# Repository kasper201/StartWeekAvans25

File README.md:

# StartWeekAvans25

The StartWeekAvans25 project is made to provide a playable game for the firstyears during the startweek. It is a continuation from [previous year's project](https://github.com/JaroWMR/Startweek.git).

# Getting Started
There are two parts to this project, the Zephyr project and Qt project.
The Zephyr project is the code which will run on the hardware and the Qt project is the code which will run on the user's PC to provide an easy way to configure and communicate with the hardware.

## Zephyr
This project has been made with Zephyr 3.7 and SDK version 16.5.

To get started you can follow the [getting started](https://docs.zephyrproject.org/3.7.0/develop/getting_started/index.html) from Zephyr, which guides you to the install process and how you can build a project.

### Digital twin
A digital twin of the hardware has been created which simulates large parts of the hardware, to allow coding and testing without the hardware. 

#### Digital twin limitations and bugs
There are some limitations on what can and cannot be done. Those can be found [here](https://docs.zephyrproject.org/3.7.0/boards/native/doc/arch_soc.html#important-limitations).

It's very likely that a busy wait loop exists in the code if the simulator hangs. This can be prevented by a adding a 'k_sleep(K_MSEC(1));' or 'k_cpu_idle();' in the loop, or using native_loop() in the code which handles adding that for the hardware only.

Currently there is also a bug with timers, meaning that the digital twin goes through a timer faster or slower. This prevents some minigames from being played properly.

The bug is less noticable in the stand-alone version, which can be found on the "stand-alone_native_sim" branch. Please check out the readme in that branch for more information about this version.

## Qt
[//]: # (Never)
The Qt application has been made with Qt 5.12. This can be installed and has been confirmed to build on both Windows and Linux.

# Building
The Zephyr project can be either build for the hardware board or for the simulator.
You can build for the hardware as follows:
```
west build -b nucleo_h743zi [whereYouveClonedTheGitRepo]\StartWeekAvans25\Project
```
You can also do a pristine build, which clears the build folder first before building everything from 0 again:
```
west build -p -b nucleo_h743zi [whereYouveClonedTheGitRepo]\StartWeekAvans25\Project
```

You can build the project the same way for the digital twin, by just replacing the board with the digital twin's board name:
```
west build -b native_sim [whereYouveClonedTheGitRepo]\StartWeekAvans25\Project
```

# Flashing and running
[//]: # (Gonna)
## Hardware
### Prerequisites
Flashing the hardware with "west flash" requires an additional step first. You need to apply the git patch called "openocd.patch" to your Zephyr install. This can be done by following these steps:
- Download openocd.patch
- Place it in your zephyr folder
- Open the terminal, go to your zephyr folder and apply the patch with
```
git apply openocd.patch
```

After this you can program the hardware aslong as it's in bootloader mode. You can turn the hardware into bootloader mode with the following steps:

- Turn off the hardware (disconnect the battery and usb)
- Connect the debugger
- Press the Boot0 button
- Turn on the hardware 
Now the hardware is in bootloader mode and can be programmed with "west flash". 

## Digital twin
[//]: # (Give)
The digital twin can be ran on Linux machines. It has been tested and confirmed to work on Ubuntu 20.04, and also confirmed to display nothing on Arch and WSL2.
You can start it up simply by using this command from the same folder you've used "west build" in:
```
west build -t run
```

# Debugging
Both the hardware and digital twin can be debugged with GDB.
## Hardware
The nucleo board requires the STM32 gdb server and command-line toolset, which can be downloaded [from here](https://www.st.com/en/development-tools/stm32cubeclt.html?ecmp=tt9470_gl_link_feb2019&rt=um&id=UM3088). After installing the tools you can use them to set up the server and client like this:
```
Client:
arm-none-eabi-gdb.exe

Server:
ST-LINK_gdbserver.exe -d -v -t -g -cp C:\ST\STM32CubeCLT_1.18.0\STM32CubeProgrammer\bin

```

Extra documentation about the command-line tools can be found on [st's website](https://www.st.com/en/development-tools/stm32cubeclt.html?ecmp=tt9470_gl_link_feb2019&rt=um&id=UM3088#documentation).

## Digital twin
[//]: # (You)
```
gdb ./build/zephyr/zephyr.exe
```

# Testing
[//]: # (Up)
There are two ways to test this project, manual for games and automatic for all other parts of the code.
Manual testing can be enabled by setting "CONFIG_TESTMODE" to "y" in the prj.conf. After building and flashing the project as usual you'll get to see a minigame selector on the LCD. You can use the ABC buttons to navigate between minigames and use the start button to confirm the game to test.

Automatic testing is done with the help of ztests. You can build them with:
```
west build -b nucleo_h743zi [whereYouveClonedTheGitRepo]\StartWeekAvans25\Project\tests
```
Upon flashing the software on the hardware it'll start to do every selected test in a random order.
Currently the test's prj.conf is configured to test everything aside from the minigame.

You can also use Twister, Zephyr's Test Runner, to run the tests with.

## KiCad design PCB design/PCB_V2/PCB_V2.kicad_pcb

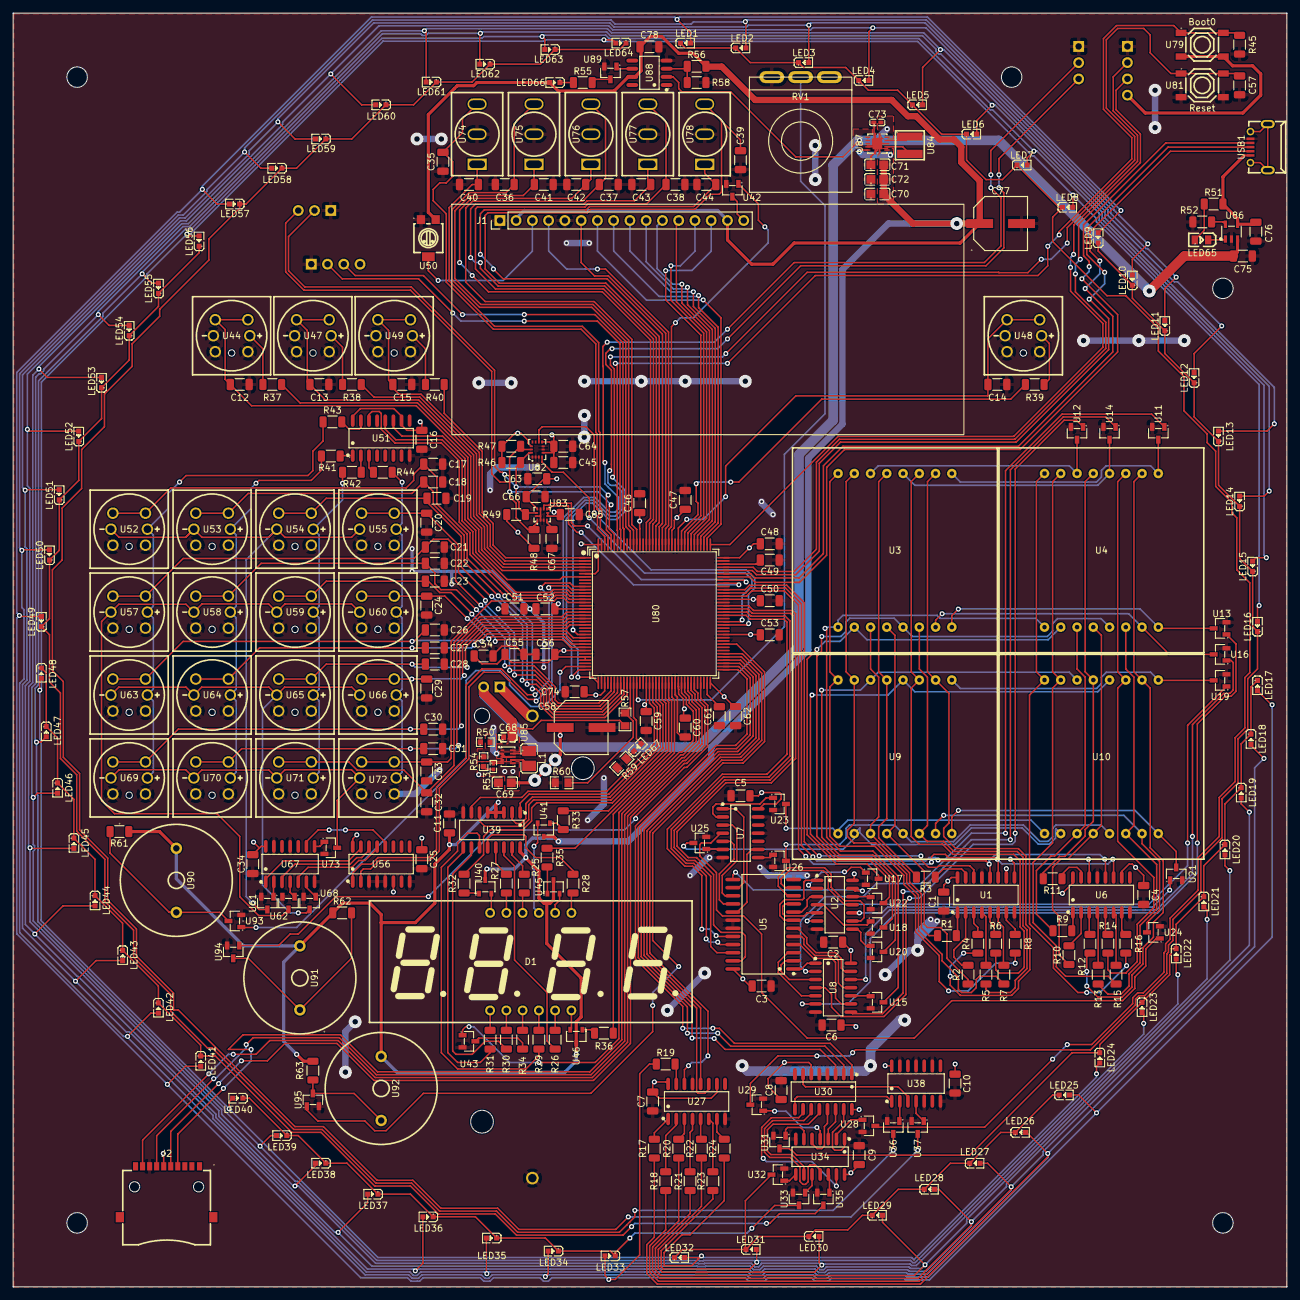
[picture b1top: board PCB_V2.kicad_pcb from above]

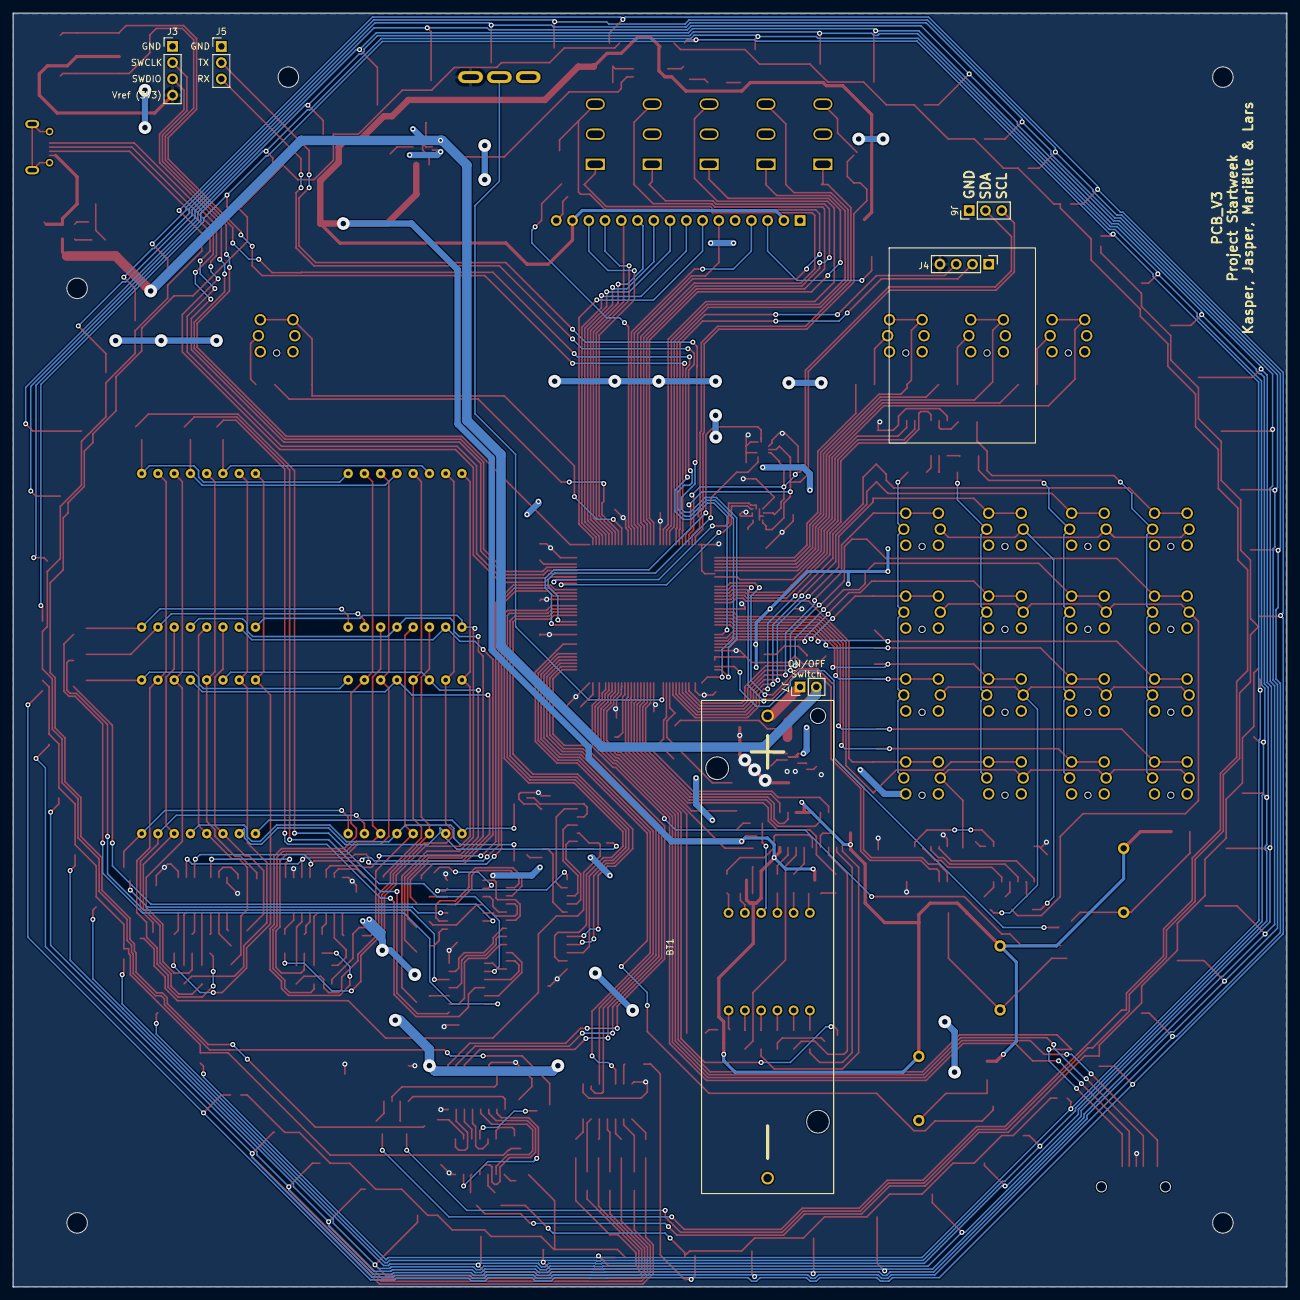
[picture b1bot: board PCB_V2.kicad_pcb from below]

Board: 2 copper layers, 199.0 x 199.0 mm, 315 parts (6 on the bottom side), 296 nets.

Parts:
BT1: Battery_Cell; Battery_Holder_Avans
C1, C2, C3, C4, C5, C6, C7, C8, C9, C10, C11, C12, C13, C14, C15, C16, C17, C18, C19, C20, C21, C22, C23, C24, C25, C26, C27, C28, C29, C30, C31, C32, C33, C34, C35, C36, C37, C38, C39, C40, C41, C42, C43, C44, C45, C46, C47, C48, C50, C52, C53, C55, C56, C57, C58, C59, C60, C62, C63, C64, C66, C67, C78: 100n; C_1206_3216Metric
C49, C61: 2u2; C_1206_3216Metric
C51, C75, C76: 4u7; C_1206_3216Metric
C54, C65: 1u; C_1206_3216Metric
C68: GRM188R60J226MEA0D; C0603
C69: GRM21BR61A226ME44L; C0805
C70, C71, C72: LMK212BJ106KG-T; C0805
C73: GRJ155R60J106ME11D; C0402
C74, C77: RVE1A471M0810; CAP-SMD_BD8.0-L8.3-W8.3-FD
D1: FJ5461BH-pure-red; LED-SEG-TH_FJ5461AH
J1: Conn_01x16; LCD_Display_AVANS
J2: SD-01A; SD-SMD_SD-01A
J3: Conn_01x04; PinHeader_1x04_P2.54mm_Vertical
J4: Conn_01x04; GPS_AVANS
J5, J6: Conn_01x03; PinHeader_1x03_P2.54mm_Vertical
J7: Conn_01x02; PinHeader_1x02_P2.54mm_Vertical
L1: LQM2HPNR47MG0L; L1008
LED1, LED2, LED3, LED4, LED5, LED6, LED7, LED8, LED9, LED10, LED11, LED12, LED13, LED14, LED15, LED16, LED17, LED18, LED19, LED20, LED21, LED22, LED23, LED24, LED25, LED26, LED27, LED28, LED29, LED30, LED31, LED32, LED33, LED34, LED35, LED36, LED37, LED38, LED39, LED40, LED41, LED42, LED43, LED44, LED45, LED46, LED47, LED48, LED49, LED50, LED51, LED52, LED53, LED54, LED55, LED56, LED57, LED58, LED59, LED60, LED61, LED62, LED63, LED64, LED66, LED67: KT-0603R; LED0603-RD
LED65: 17-21SUYC_TR8; LED0805-R-RD
R1, R2, R3, R4, R5, R6, R7, R8, R9, R10, R11, R12, R13, R14, R15, R16: 220; R_1206_3216Metric
R17, R18, R19, R20, R21, R22, R23, R24: 100; R_1206_3216Metric
R25, R26, R27, R28, R29, R30, R31, R34: 270; R_1206_3216Metric
R32, R33, R35, R36: 390; R_1206_3216Metric
R37, R38, R39, R40, R41, R42, R43, R44: 150; R_1206_3216Metric
R45, R46, R47, R48, R49: 10k; R_1206_3216Metric
R50: RC0603FR-0791KL; R0603
R51: 330; R_1206_3216Metric
R52: 2k2; R_1206_3216Metric
R53: CRCW0402100KFKED; R0402
R54: RC0603FR-07511KL; R0603
R55, R61, R62, R63: 470; R_1206_3216Metric
R56: 16k; R_1206_3216Metric
R57: 10k; R0805
R58: 20k; R_1206_3216Metric
R59: 200; R0805
R60: 18k; R0805
RV1: 50k; Potmeter_THT_Avans
U1, U6, U27, U51: SN74HC595DR; SOIC-16_L9.9-W3.9-P1.27-LS6.0-BL
U2, U7, U8, U34, U38, U67: SN74HC04DR; SOIC-14_L8.7-W3.9-P1.27-LS6.0-BL
U3, U4, U9, U10: SZ421288N_64; LED-SEG-TH_SZ421288N-64
U5: CD74HC154M96; SOIC-24_L15.4-W7.5-P1.27-LS10.3-BL
U11, U12, U13, U14, U15, U16, U17, U18, U19, U20, U21, U22, U23, U24, U25, U26, U28, U29, U31, U32, U33, U35, U36, U37, U42, U43, U61, U62, U68, U73, U89, U93, U94, U95: BSN20BKR; SOT-23-3_L2.9-W1.3-P1.90-LS2.4-BR
U30, U56: SN74HC138DR; SOIC-16_L9.9-W3.9-P1.27-LS6.0-BL
U39: SN74LS47DR; SOIC-16_L9.9-W3.9-P1.27-LS6.0-BL
U40, U41, U45, U46: BC817_C475629; SOT-23-3_L2.9-W1.4-P1.90-LS2.6-BR
U44, U47, U48, U49, U52, U53, U54, U55, U57, U58, U59, U60, U63, U64, U65, U66, U69, U70, U71, U72: K6-6271D04; SW-TH_K6-6271DXX
U50: 3314G-1-203E; RES-ADJ-SMD_3314G-1-103E
U74, U75, U76, U77, U78: MT-0-102-A101-M200-RS+PJ; SW-TH_MT-0-103-A101-M200-RS
U79, U81: TS-1187A-B-A-B; SW-SMD_4P-L5.1-W5.1-P3.70-LS6.5-TL-2
U80: STM32H743ZIT6; LQFP-144_L20.0-W20.0-P0.50-LS22.0-BL
U82: LSM6DSOWTR; LGA-14L_L3.0-W2.5-P0.50-TL
U83: LIS3MDLTR; LGA-12_L2.0-W2.0-P0.50-BL
U84: VLS4012ET-3R3M; IND-SMD_L4.0-W4.0_VLS4012ET
U85: TPS63802DLAR; VSON-10_L3.0-W2.0-P0.50-TL
U86: MCP73831T-2ACI_OT; SOT-23-5_L3.0-W1.7-P0.95-LS2.8-BL
U87: TPS63002DRCR; VSON-10_L3.0-W3.0-P0.50-TL-EP_TPS62410DRCR
U88: LF356MX; SOP-8_L4.9-W3.9-P1.27-LS6.0-BL
U90, U91, U92: HNR-1707; BUZ-TH_BD17.0-P10.00-D0.9
USB1: micro_USBFemale; MICRO-USB-SMD_5P-P0.65-H-F_C10418

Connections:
3D_Compass_Data_Ready: U80.101 (PA9), U83.8 (DRDY)
3D_Compass_I2C_SCL: J6.3, R47.1, R48.1, U80.139 (PB8), U82.13 (SCL), U83.1 (SCL/SPC)
3D_Compass_I2C_SDA: J6.2, R46.1, R49.1, U80.140 (PB9), U82.14 (SDA), U83.11 (SDA/SDI/SDO)
3D_Compass_Interupt: U80.100 (PA8), U83.7 (INT)
4X4_LED_Buttons_Button_1: C17.1, U52.3, U52.4, U80.46 (PB0)
4X4_LED_Buttons_Button_2: C18.1, U53.3, U53.4, U80.45 (PC5)
4X4_LED_Buttons_Button_3: C19.1, U54.3, U54.4, U80.44 (PC4)
4X4_LED_Buttons_Button_4: C20.1, U55.3, U55.4, U80.43 (PA7)
4X4_LED_Buttons_Button_5: C21.1, U57.3, U57.4, U80.42 (PA6)
4X4_LED_Buttons_Button_6: C22.1, U58.3, U58.4, U80.41 (PA5)
4X4_LED_Buttons_Button_7: C23.1, U59.3, U59.4, U80.29 (PC3_C)
4X4_LED_Buttons_Button_8: C24.1, U60.3, U60.4, U80.28 (PC2_C)
4X4_LED_Buttons_Button_9: C26.1, U63.3, U63.4, U80.27 (PC1)
4X4_LED_Buttons_Button_10: C27.1, U64.3, U64.4, U80.26 (PC0)
4X4_LED_Buttons_Button_11: C28.1, U65.3, U65.4, U80.22 (PF10)
4X4_LED_Buttons_Button_12: C29.1, U66.3, U66.4, U80.21 (PF9)
4X4_LED_Buttons_Button_13: C30.1, U69.3, U69.4, U80.20 (PF8)
4X4_LED_Buttons_Button_14: C31.1, U70.3, U70.4, U80.19 (PF7)
4X4_LED_Buttons_Button_15: C32.1, U71.3, U71.4, U80.18 (PF6)
4X4_LED_Buttons_Button_16: C33.1, U72.3, U72.4, U80.15 (PF5)
4X4_LED_Buttons_MUX_A: U56.1 (A), U80.10 (PF0)
4X4_LED_Buttons_MUX_B: U56.2 (B), U80.11 (PF1)
4X4_LED_Buttons_shift_clock: U51.11 (SRCLK), U80.12 (PF2)
4X4_LED_Buttons_shift_data_in: U51.14 (SER), U80.14 (PF4)
4X4_LED_Buttons_shift_output_enable: U51.12 (RCLK), U80.13 (PF3)
7-segment_BCD_A: U39.7 (A), U80.53 (PF13)
7-segment_BCD_B: U39.1 (B), U80.54 (PF14)
7-segment_BCD_C: U39.2 (C), U80.55 (PF15)
7-segment_BCD_D: U39.6 (D), U80.56 (PG0)
7-segment_Decimal_Point: U43.1 (G), U80.63 (PE10)
7-segment_MUX_DIG1: R32.2, U80.57 (PG1)
7-segment_MUX_DIG2: R33.2, U80.58 (PE7)
7-segment_MUX_DIG3: R35.2, U80.59 (PE8)
7-segment_MUX_DIG4: R36.2, U80.60 (PE9)
16X16_MUX_A0: U5.23 (A0), U80.93 (PG8)
16X16_MUX_A1: U5.22 (A1), U80.92 (PG7)
16X16_MUX_A2: U5.21 (A2), U80.91 (PG6)
16X16_MUX_A3: U5.20 (A3), U80.90 (PG5)
16X16_shift_clock: U1.11 (SRCLK), U6.11 (SRCLK), U80.96 (PC6)
16X16_shift_data_in: U1.14 (SER), U80.98 (PC8)
16X16_shift_output_enable: U1.12 (RCLK), U6.12 (RCLK), U80.97 (PC7)
+3V3: C1.1, C2.1, C3.1, C4.1, C5.1, C6.1, C7.1, C8.1, C9.1, C10.1, C16.1, C25.1, C34.1, C45.1, C46.1, C47.1, C48.1, C50.1, C51.1, C52.1, C53.1, C54.1, C55.1, C56.1, C58.1, C59.1, C60.1, C62.1, C63.1, C64.1, C65.1, C66.1, C69.2, C74.1, J2.4 (VDD), J3.4, J4.4, R46.2, R47.2, R48.2, R49.2, R53.2, R54.2, RV1.3, U1.10 (SRCLR#), U1.16 (VCC), U2.14 (VCC), U5.24 (VCC), U6.10 (SRCLR#), U6.16 (VCC), U7.14 (VCC), U8.14 (VCC), U27.10 (SRCLR#), U27.16 (VCC), U30.6 (G1), U30.16 (VCC), U34.14 (VCC), U38.14 (VCC), U51.10 (SRCLR#), U51.16 (VCC), U56.6 (G1), U56.16 (VCC), U67.14 (VCC), U79.3 (C), U79.4 (D), U80.6 (VBAT), U80.17 (VDD), U80.30 (VDD), U80.32 (VREF+), U80.33 (VDDA), U80.39 (VDD), U80.52 (VDD), U80.62 (VDD), U80.72 (VDD), U80.84 (VDD), U80.95 (VDDUSB), U80.108 (VDD), U80.121 (VDD), U80.131 (VDD), U80.143 (PDR_ON), U80.144 (VDD), U82.5 (VDDIO), U82.8 (VDD), U82.12 (CS), U83.5 (Vdd), U83.6 (Vdd_IO), U83.10 (CS), U85.6 (VOUT)
+5V: C11.1, C70.2, C71.2, C72.2, C77.1, C78.1, J1.2, J1.15, LED66.2 (A), R56.2, R61.1, R62.1, R63.1, U39.3 (LT#), U39.4 (BI#/RBO#), U39.5 (RBI#), U39.16 (VCC), U40.3 (C), U41.3 (C), U45.3 (C), U46.3 (C), U50.3, U87.1 (VOUT), U87.10 (FB), U88.7 (V+), U90.1, U91.1, U92.1
+BATT: C68.2, C73.2, C75.1, J7.2, R57.2, U85.1 (EN), U85.10 (VIN), U86.3 (VBAT), U87.5 (VIN), U87.6 (EN), U87.7 (PS/SYNC), U87.8 (VINA), U88.2 (-IN)
A: D1.11 (A), R27.1
ABC_Buttons_A_Button: C12.1, U44.3, U44.4, U80.7 (PC13)
ABC_Buttons_A_LED: R37.1, U80.5 (PE6)
ABC_Buttons_B_Button: C13.1, U47.3, U47.4, U80.4 (PE5)
ABC_Buttons_B_LED: R38.1, U80.3 (PE4)
ABC_Buttons_C_Button: C15.1, U49.3, U49.4, U80.2 (PE3)
ABC_Buttons_C_LED: R40.1, U80.1 (PE2)
B: D1.7 (B), R28.1
BOOT0: R45.2, U79.1 (A), U79.2 (B), U80.138 (BOOT0)
Battery_Low_LED: LED67.2 (A), U80.48 (PB2)
Battery_Voltage: R57.1, R60.2, U80.47 (PB1)
C: D1.4 (C), R29.1
D: D1.2 (D), R30.1
DEBUG_UART_RX: J5.3, U80.37 (PA3)
DEBUG_UART_TX: J5.2, U80.36 (PA2)
DIG1: D1.12 (DIG1), U40.2 (E)
DIG2: D1.9 (DIG2), U41.2 (E)
DIG3: D1.8 (DIG3), U45.2 (E)
DIG4: D1.6 (DIG4), U46.2 (E)
DP: D1.3 (DP), R34.2
E: D1.1 (E), R31.1
F: D1.10 (F), R25.1
G: D1.5 (G), R26.1
GND: BT1.2 (-), C1.2, C2.2, C3.2, C4.2, C5.2, C6.2, C7.2, C8.2, C9.2, C10.2, C11.2, C12.2, C13.2, C14.2, C15.2, C16.2, C17.2, C18.2, C19.2, C20.2, C21.2, C22.2, C23.2, C24.2, C25.2, C26.2, C27.2, C28.2, C29.2, C30.2, C31.2, C32.2, C33.2, C34.2, C35.1, C36.1, C37.1, C38.1, C39.1, C40.1, C41.1, C42.1, C43.1, C44.1, C45.2, C46.2, C47.2, C48.2, C49.2, C50.2, C51.2, C52.2, C53.2, C54.2, C55.2, C56.2, C57.2, C58.2, C59.2, C60.2, C61.2, C62.2, C63.2, C64.2, C65.2, C66.2, C67.2, C68.1, C69.1, C70.1, C71.1, C72.1, C73.1, C74.2, C75.2, C76.2, C77.2, C78.2, J1.1, J1.5, J2.6 (VSS), J3.1, J4.1, J5.1, J6.1, R45.1, R50.1, R52.1, R58.1, R59.1, R60.1, RV1.1, U1.8 (GND), U1.13 (OE#), U2.7 (GND), U5.12 (GND), U5.18 (E1#), U5.19 (E2#), U6.8 (GND), U6.13 (OE#), U7.7 (GND), U7.11 (5A), U7.13 (6A), U8.7 (GND), U11.2 (S), U12.2 (S), U13.2 (S), U14.2 (S), U15.2 (S), U16.2 (S), U17.2 (S), U18.2 (S), U19.2 (S), U20.2 (S), U21.2 (S), U22.2 (S), U23.2 (S), U24.2 (S), U25.2 (S), U26.2 (S), U27.8 (GND), U27.13 (OE#), U28.2 (S), U29.2 (S), U30.4 (G2A#), U30.5 (G2B#), U30.8 (GND), U31.2 (S), U32.2 (S), U33.2 (S), U34.7 (GND), U35.2 (S), U36.2 (S), U37.2 (S), U38.5 (3A), U38.7 (GND), U38.9 (4A), U38.11 (5A), U38.13 (6A), U39.8 (GND), U42.2 (S), U43.2 (S), U44.1, U44.2, U44.5, U47.1, U47.2, U47.5, U48.1, U48.2, U48.5, U49.1, U49.2, U49.5, U50.1, U51.8 (GND), U51.13 (OE#), U52.1, U52.2, U53.1, U53.2, U54.1, U54.2, U55.1, U55.2, U56.3 (C), U56.4 (G2A#), U56.5 (G2B#), U56.8 (GND), U57.1, U57.2, U58.1, U58.2, U59.1, U59.2, U60.1, U60.2, U61.2 (S), U62.2 (S), U63.1, U63.2, U64.1, U64.2, U65.1, U65.2, U66.1, U66.2, U67.7 (GND), U67.11 (5A), U67.13 (6A), U68.2 (S), U69.1, U69.2, U70.1, U70.2, U71.1, U71.2, U72.1, U72.2, U73.2 (S), U74.2, U75.2, U76.2, U77.2, U78.2, U80.16 (VSS), U80.31 (VSSA), U80.38 (VSS), U80.51 (VSS), U80.61 (VSS), U80.83 (VSS), U80.94 (VSS), U80.107 (VSS), U80.120 (VSS), U80.130 (VSS), U81.3 (C), U81.4 (D), U82.1 (SDO/SA0), U82.2 (SDx), U82.3 (SCx), U82.6 (GND), U82.7 (GND), U83.2 (Res), U83.3 (GND), U83.9 (SD0/SA1), U83.12 (Res), U85.2 (MODE), U85.3 (AGND), U85.8 (GND), U86.2 (VSS), U87.3 (PGND), U87.9 (GND), U87.11 (EP), U88.4 (V-), U89.2 (S), U93.2 (S), U94.2 (S), U95.2 (S), USB1.5 (V-)
GNSS_RX: J4.3, U80.136 (PB6)
GNSS_TX: J4.2, U80.137 (PB7)
Gyro_Interupt1: U80.88 (PG3), U82.4 (INT1)
Gyro_Interupt2: U80.87 (PG2), U82.9 (INT2)
LCD_Display_Backlight_Enable: U42.1 (G), U80.122 (PD6)
LCD_Display_D0: J1.7, U80.110 (PA15)
LCD_Display_D1: J1.8, U80.111 (PC10)
LCD_Display_D2: J1.9, U80.112 (PC11)
LCD_Display_D3: J1.10, U80.113 (PC12)
LCD_Display_D4: J1.11, U80.114 (PD0)
LCD_Display_D5: J1.12, U80.115 (PD1)
LCD_Display_D6: J1.13, U80.116 (PD2)
LCD_Display_D7: J1.14, U80.117 (PD3)
LCD_Display_E: J1.6, U80.124 (PG9)
LCD_Display_RS: J1.4, U80.123 (PD7)
LED_Circle_MUX_A: U30.1 (A), U80.73 (PB12)
LED_Circle_MUX_B: U30.2 (B), U80.74 (PB13)
LED_Circle_MUX_C: U30.3 (C), U80.75 (PB14)
LED_Circle_shift_clock: U27.11 (SRCLK), U80.76 (PB15)
LED_Circle_shift_data_in: U27.14 (SER), U80.78 (PD9)
LED_Circle_shift_output_enable: U27.12 (RCLK), U80.77 (PD8)
unnamed: BT1.1 (+), J7.1
unnamed: C49.1, U80.106 (Vcap_2)
unnamed: C61.1, U80.71 (Vcap_1)
unnamed: C67.1, U83.4 (C1)
unnamed: J1.3, U50.2
unnamed: J1.16, U42.3 (D)
unnamed: L1.1, U85.9 (L1)
unnamed: L1.2, U85.7 (L2)
unnamed: LED65.1 (+), R51.1
unnamed: LED65.2 (-), U86.1 (STAT)
unnamed: LED66.1 (K), R55.2
unnamed: LED67.1 (K), R59.2
unnamed: R1.2, U1.1 (QB)
unnamed: R2.2, U1.2 (QC)
unnamed: R3.1, U1.15 (QA)
unnamed: R4.2, U1.3 (QD)
unnamed: R5.2, U1.4 (QE)
unnamed: R6.2, U1.5 (QF)
unnamed: R7.2, U1.6 (QG)
unnamed: R8.2, U1.7 (QH)
unnamed: R9.2, U6.1 (QB)
unnamed: R10.2, U6.2 (QC)
unnamed: R11.1, U6.15 (QA)
unnamed: R12.2, U6.3 (QD)
unnamed: R13.2, U6.4 (QE)
unnamed: R14.2, U6.5 (QF)
unnamed: R15.2, U6.6 (QG)
unnamed: R16.2, U6.7 (QH)
unnamed: R17.2, U27.1 (QB)
unnamed: R18.2, U27.2 (QC)
unnamed: R19.1, U27.15 (QA)
unnamed: R20.2, U27.3 (QD)
unnamed: R21.2, U27.4 (QE)
unnamed: R22.2, U27.5 (QF)
unnamed: R23.2, U27.6 (QG)
unnamed: R24.2, U27.7 (QH)
unnamed: R25.2, U39.15 (f)
unnamed: R26.2, U39.14 (g)
unnamed: R27.2, U39.13 (a)
unnamed: R28.2, U39.12 (b)
unnamed: R29.2, U39.11 (c)
unnamed: R30.2, U39.10 (d)
unnamed: R31.2, U39.9 (e)
unnamed: R32.1, U40.1 (B)
unnamed: R33.1, U41.1 (B)
unnamed: R34.1, U43.3 (D)
unnamed: R35.1, U45.1 (B)
unnamed: R36.1, U46.1 (B)
unnamed: R37.2, U44.6
unnamed: R38.2, U47.6
unnamed: R39.2, U48.6
unnamed: R40.2, U49.6
unnamed: R41.1, U51.1 (QB)
unnamed: R42.1, U51.2 (QC)
unnamed: R43.2, U51.15 (QA)
unnamed: R44.1, U51.3 (QD)
unnamed: R50.2, R54.1, U85.4 (FB)
unnamed: R52.2, U86.5 (PROG)
unnamed: R53.1, U85.5 (PG)
unnamed: R55.1, U89.3 (D)
unnamed: R56.1, R58.2, U88.3 (+IN)
unnamed: R61.2, U90.2, U93.3 (D)
unnamed: R62.2, U91.2, U94.3 (D)
unnamed: R63.2, U92.2, U95.3 (D)
unnamed: U1.9 (QH#), U6.14 (SER)
unnamed: U84.1, U87.4 (L1)
unnamed: U84.2, U87.2 (L2)
unnamed: U88.6 (OUT), U89.1 (G)
Reset: C57.1, U80.25 (NRST), U81.1 (A), U81.2 (B)
Rotary_Switch: RV1.2, U80.49 (PF11)
SD_Card_CS: J2.2 (CD/DAT3), U80.64 (PE11)
SD_Card_DI: J2.3 (CMD), U80.67 (PE14)
SD_Card_DO: J2.7 (DAT0), U80.66 (PE13)
SD_Card_SCLK: J2.5 (CLK), U80.65 (PE12)
SWCLK: J3.2, U80.109 (PA14)
SWDIO: J3.3, U80.105 (PA13)
Start_Button_Button: C14.1, U48.3, U48.4, U80.119 (PD5)
Start_Button_LED: R39.1, U80.118 (PD4)
Switches_Switch_1_OFF: C40.2, U74.1, U80.141 (PE0)
Switches_Switch_1_ON: C35.2, U74.3, U80.142 (PE1)
Switches_Switch_2_OFF: C41.2, U75.1, U80.133 (PB3)
Switches_Switch_2_ON: C36.2, U75.3, U80.134 (PB4)
Switches_Switch_3_OFF: C42.2, U76.1, U80.129 (PG14)
Switches_Switch_3_ON: C37.2, U76.3, U80.132 (PG15)
Switches_Switch_4_OFF: C43.2, U77.1, U80.127 (PG12)
Switches_Switch_4_ON: C38.2, U77.3, U80.128 (PG13)
Switches_Switch_5_OFF: C44.2, U78.1, U80.125 (PG10)
Switches_Switch_5_ON: C39.2, U78.3, U80.126 (PG11)
USB_D+: U80.104 (PA12), USB1.3 (D+)
USB_D-: U80.103 (PA11), USB1.2 (D-)
USB_ID: U80.102 (PA10), USB1.4 (ID)
VBUS: C76.1, R51.2, U86.4 (VDD), USB1.1 (V+)
buzzer1: U80.35 (PA1), U93.1 (G)
buzzer2: U80.69 (PB10), U94.1 (G)
buzzer3: U80.81 (PD12), U95.1 (G)
c_1: LED1.2 (A), LED9.2 (A), LED17.2 (A), LED25.2 (A), LED33.2 (A), LED41.2 (A), LED49.2 (A), LED57.2 (A), R19.2
c_2: LED2.2 (A), LED10.2 (A), LED18.2 (A), LED26.2 (A), LED34.2 (A), LED42.2 (A), LED50.2 (A), LED58.2 (A), R17.1
c_3: LED3.2 (A), LED11.2 (A), LED19.2 (A), LED27.2 (A), LED35.2 (A), LED43.2 (A), LED51.2 (A), LED59.2 (A), R18.1
c_4: LED4.2 (A), LED12.2 (A), LED20.2 (A), LED28.2 (A), LED36.2 (A), LED44.2 (A), LED52.2 (A), LED60.2 (A), R20.1
c_5: LED5.2 (A), LED13.2 (A), LED21.2 (A), LED29.2 (A), LED37.2 (A), LED45.2 (A), LED53.2 (A), LED61.2 (A), R21.1
c_6: LED6.2 (A), LED14.2 (A), LED22.2 (A), LED30.2 (A), LED38.2 (A), LED46.2 (A), LED54.2 (A), LED62.2 (A), R22.1
c_7: LED7.2 (A), LED15.2 (A), LED23.2 (A), LED31.2 (A), LED39.2 (A), LED47.2 (A), LED55.2 (A), LED63.2 (A), R23.1
c_8: LED8.2 (A), LED16.2 (A), LED24.2 (A), LED32.2 (A), LED40.2 (A), LED48.2 (A), LED56.2 (A), LED64.2 (A), R24.1
co_1: R43.1, U52.6, U57.6, U63.6, U69.6
co_2: R41.2, U53.6, U58.6, U64.6, U70.6
co_3: R42.2, U54.6, U59.6, U65.6, U71.6
co_4: R44.2, U55.6, U60.6, U66.6, U72.6
col_1: R3.2, U3.13, U9.13
col_2: R1.1, U3.3, U9.3
col_3: R2.1, U3.4, U9.4
col_4: R4.1, U3.10, U9.10
col_5: R5.1, U3.6, U9.6
col_6: R6.1, U3.11, U9.11
col_7: R7.1, U3.15, U9.15
col_8: R8.1, U3.16, U9.16
col_9: R11.2, U4.13, U10.13
col_10: R9.1, U4.3, U10.3
col_11: R10.1, U4.4, U10.4
col_12: R12.1, U4.10, U10.10
col_13: R13.1, U4.6, U10.6
col_14: R14.1, U4.11, U10.11
col_15: R15.1, U4.15, U10.15
col_16: R16.1, U4.16, U10.16
gate_r_1: U28.1 (G), U34.2 (1Y)
gate_r_1_inv: U30.15 (Y0), U34.1 (1A)
gate_r_2: U29.1 (G), U34.4 (2Y)
gate_r_2_inv: U30.14 (Y1), U34.3 (2A)
gate_r_3: U31.1 (G), U34.6 (3Y)
gate_r_3_inv: U30.13 (Y2), U34.5 (3A)
gate_r_4: U32.1 (G), U34.8 (4Y)
gate_r_4_inv: U30.12 (Y3), U34.9 (4A)
gate_r_5: U33.1 (G), U34.10 (5Y)
gate_r_5_inv: U30.11 (Y4), U34.11 (5A)
gate_r_6: U34.12 (6Y), U35.1 (G)
gate_r_6_inv: U30.10 (Y5), U34.13 (6A)
gate_r_7: U36.1 (G), U38.2 (1Y)
gate_r_7_inv: U30.9 (Y6), U38.1 (1A)
gate_r_8: U37.1 (G), U38.4 (2Y)
gate_r_8_inv: U30.7 (Y7), U38.3 (2A)
gate_ro_1: U61.1 (G), U67.2 (1Y)
gate_ro_1_inv: U56.15 (Y0), U67.1 (1A)
gate_ro_2: U62.1 (G), U67.4 (2Y)
gate_ro_2_inv: U56.14 (Y1), U67.3 (2A)
gate_ro_3: U67.6 (3Y), U68.1 (G)
gate_ro_3_inv: U56.13 (Y2), U67.5 (3A)
gate_ro_4: U67.8 (4Y), U73.1 (G)
gate_ro_4_inv: U56.12 (Y3), U67.9 (4A)
gate_row_1: U8.2 (1Y), U11.1 (G)
gate_row_1_inv: U5.1 (Y0#), U8.1 (1A)
gate_row_2: U8.4 (2Y), U12.1 (G)
gate_row_2_inv: U5.2 (Y1#), U8.3 (2A)
gate_row_3: U8.6 (3Y), U13.1 (G)
gate_row_3_inv: U5.3 (Y2#), U8.5 (3A)
gate_row_4: U8.8 (4Y), U14.1 (G)
gate_row_4_inv: U5.4 (Y3#), U8.9 (4A)
gate_row_5: U8.10 (5Y), U15.1 (G)
gate_row_5_inv: U5.5 (Y4#), U8.11 (5A)
gate_row_6: U8.12 (6Y), U16.1 (G)
gate_row_6_inv: U5.6 (Y5#), U8.13 (6A)
gate_row_7: U2.2 (1Y), U17.1 (G)
gate_row_7_inv: U2.1 (1A), U5.7 (Y6#)
gate_row_8: U2.4 (2Y), U18.1 (G)
gate_row_8_inv: U2.3 (2A), U5.8 (Y7#)
gate_row_9: U2.6 (3Y), U19.1 (G)
gate_row_9_inv: U2.5 (3A), U5.9 (Y8#)
gate_row_10: U2.8 (4Y), U20.1 (G)
gate_row_10_inv: U2.9 (4A), U5.10 (Y9#)
gate_row_11: U2.10 (5Y), U21.1 (G)
gate_row_11_inv: U2.11 (5A), U5.11 (Y10#)
gate_row_12: U2.12 (6Y), U22.1 (G)
gate_row_12_inv: U2.13 (6A), U5.13 (Y11#)
gate_row_13: U7.2 (1Y), U23.1 (G)
gate_row_13_inv: U5.14 (Y12#), U7.1 (1A)
gate_row_14: U7.4 (2Y), U24.1 (G)
gate_row_14_inv: U5.15 (Y13#), U7.3 (2A)
gate_row_15: U7.6 (3Y), U25.1 (G)
gate_row_15_inv: U5.16 (Y14#), U7.5 (3A)
gate_row_16: U7.8 (4Y), U26.1 (G)
gate_row_16_inv: U5.17 (Y15#), U7.9 (4A)
r_1: LED1.1 (K), LED2.1 (K), LED3.1 (K), LED4.1 (K), LED5.1 (K), LED6.1 (K), LED7.1 (K), LED8.1 (K), U28.3 (D)
r_2: LED9.1 (K), LED10.1 (K), LED11.1 (K), LED12.1 (K), LED13.1 (K), LED14.1 (K), LED15.1 (K), LED16.1 (K), U29.3 (D)
r_3: LED17.1 (K), LED18.1 (K), LED19.1 (K), LED20.1 (K), LED21.1 (K), LED22.1 (K), LED23.1 (K), LED24.1 (K), U31.3 (D)
r_4: LED25.1 (K), LED26.1 (K), LED27.1 (K), LED28.1 (K), LED29.1 (K), LED30.1 (K), LED31.1 (K), LED32.1 (K), U32.3 (D)
r_5: LED33.1 (K), LED34.1 (K), LED35.1 (K), LED36.1 (K), LED37.1 (K), LED38.1 (K), LED39.1 (K), LED40.1 (K), U33.3 (D)
r_6: LED41.1 (K), LED42.1 (K), LED43.1 (K), LED44.1 (K), LED45.1 (K), LED46.1 (K), LED47.1 (K), LED48.1 (K), U35.3 (D)
r_7: LED49.1 (K), LED50.1 (K), LED51.1 (K), LED52.1 (K), LED53.1 (K), LED54.1 (K), LED55.1 (K), LED56.1 (K), U36.3 (D)
r_8: LED57.1 (K), LED58.1 (K), LED59.1 (K), LED60.1 (K), LED61.1 (K), LED62.1 (K), LED63.1 (K), LED64.1 (K), U37.3 (D)
ro_1: U52.5, U53.5, U54.5, U55.5, U61.3 (D)
ro_2: U57.5, U58.5, U59.5, U60.5, U62.3 (D)
ro_3: U63.5, U64.5, U65.5, U66.5, U68.3 (D)
ro_4: U69.5, U70.5, U71.5, U72.5, U73.3 (D)
row_1: U3.9, U4.9, U11.3 (D)
row_2: U3.14, U4.14, U12.3 (D)
row_3: U3.8, U4.8, U13.3 (D)
row_4: U3.12, U4.12, U14.3 (D)
row_5: U3.1, U4.1, U15.3 (D)
row_6: U3.7, U4.7, U16.3 (D)
row_7: U3.2, U4.2, U17.3 (D)
row_8: U3.5, U4.5, U18.3 (D)
row_9: U9.9, U10.9, U19.3 (D)
row_10: U9.14, U10.14, U20.3 (D)
row_11: U9.8, U10.8, U21.3 (D)
row_12: U9.12, U10.12, U22.3 (D)
row_13: U9.1, U10.1, U23.3 (D)
row_14: U9.7, U10.7, U24.3 (D)
row_15: U9.2, U10.2, U25.3 (D)
row_16: U9.5, U10.5, U26.3 (D)

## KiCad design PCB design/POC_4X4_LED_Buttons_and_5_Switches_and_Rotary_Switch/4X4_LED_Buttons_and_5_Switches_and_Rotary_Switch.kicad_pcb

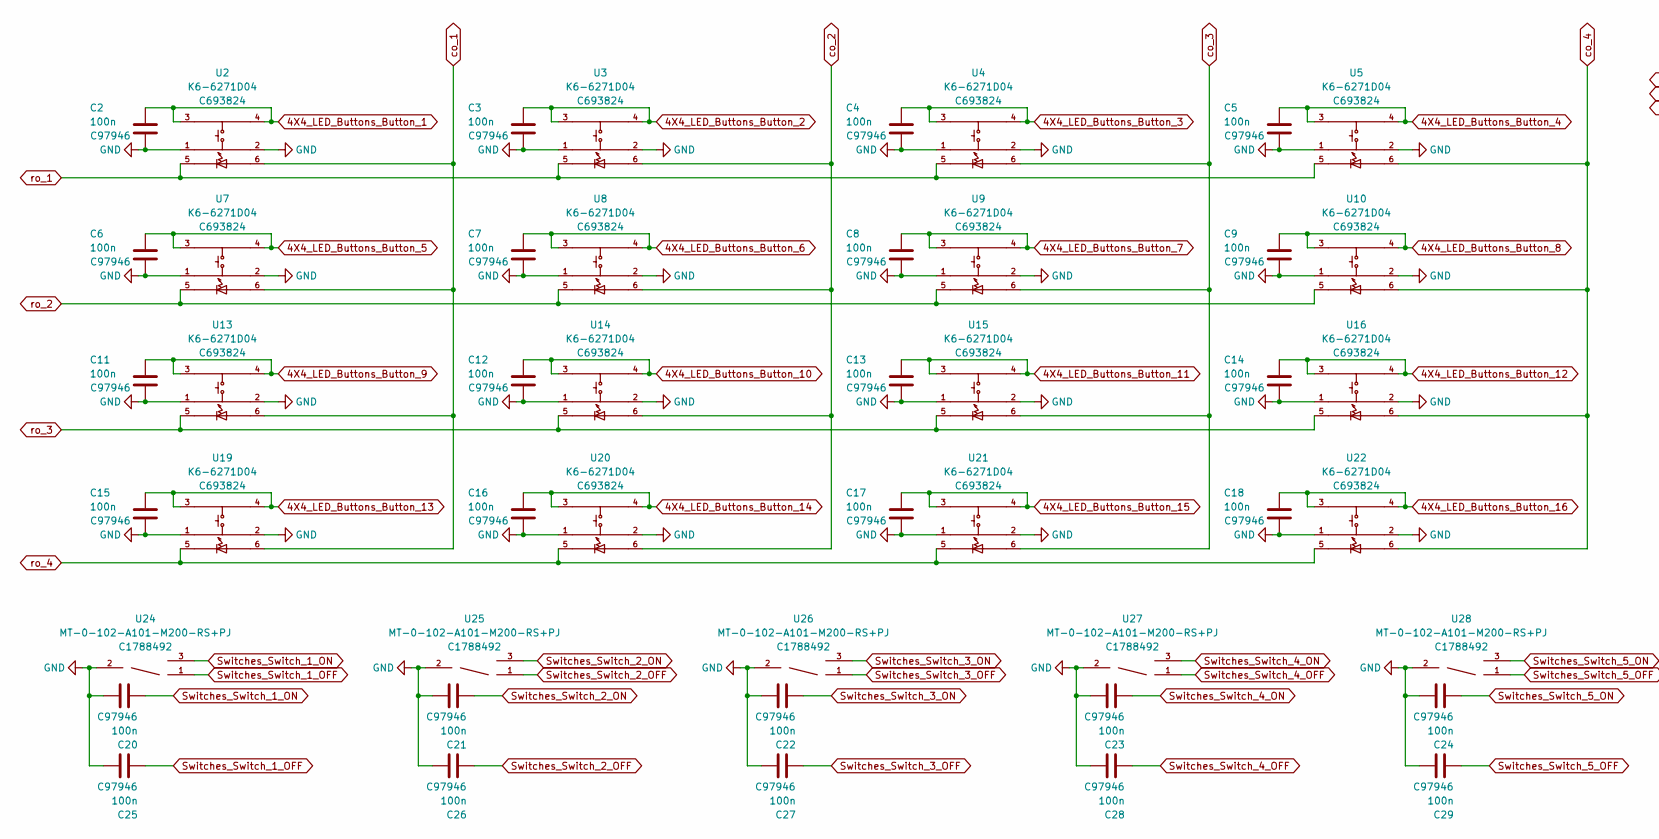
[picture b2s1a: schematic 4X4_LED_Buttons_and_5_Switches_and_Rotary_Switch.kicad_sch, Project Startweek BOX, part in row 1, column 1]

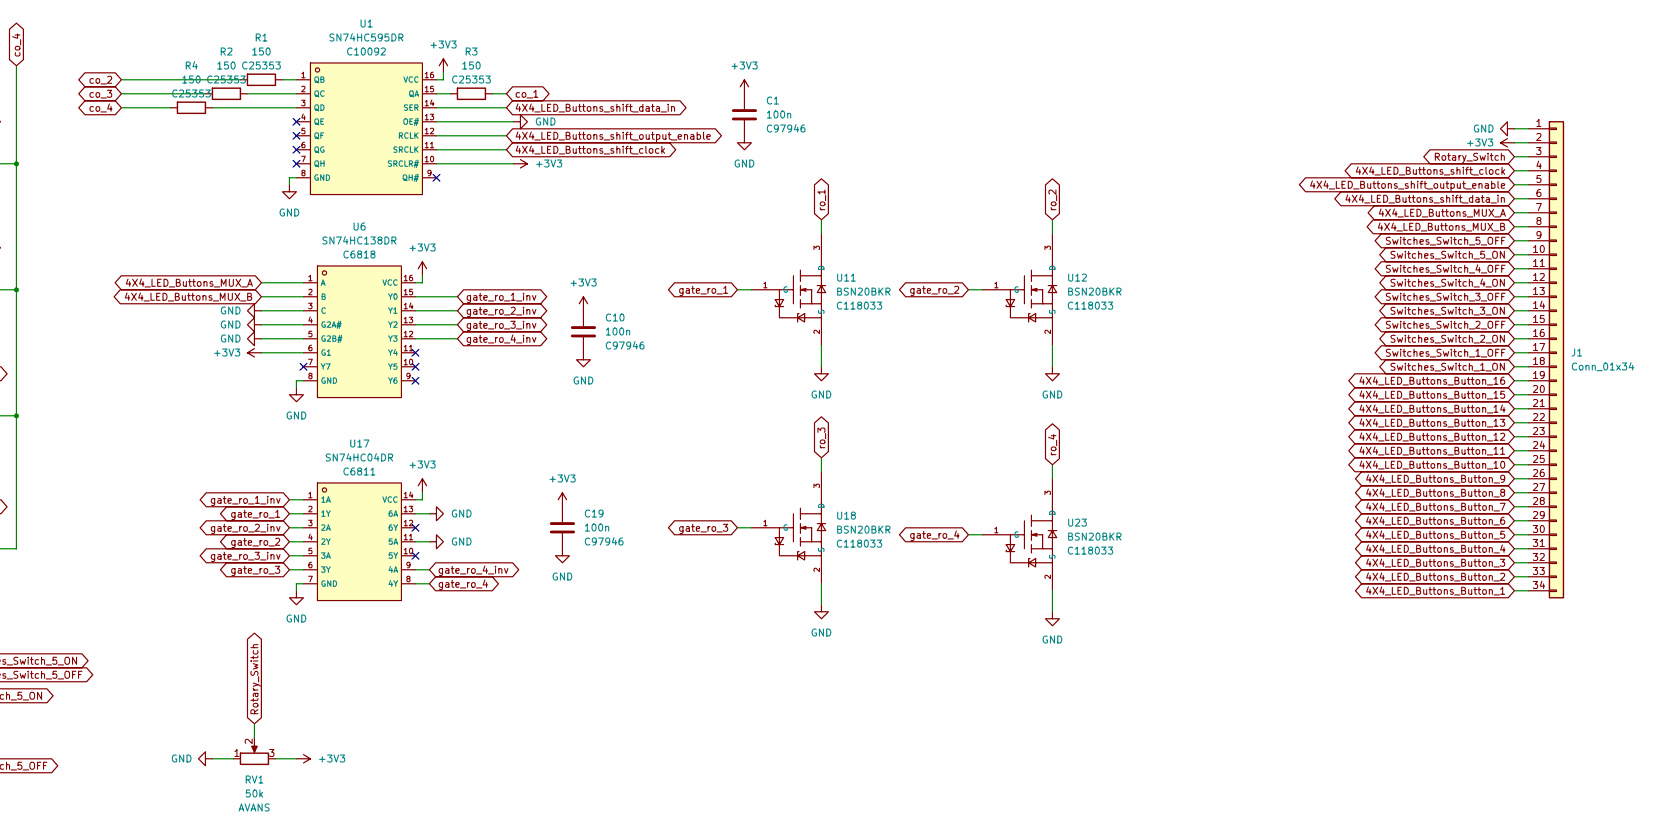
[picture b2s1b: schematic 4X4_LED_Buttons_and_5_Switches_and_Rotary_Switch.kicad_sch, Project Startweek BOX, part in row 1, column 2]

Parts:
C1, C2, C3, C4, C5, C6, C7, C8, C9, C10, C11, C12, C13, C14, C15, C16, C17, C18, C19, C20, C21, C22, C23, C24, C25, C26, C27, C28, C29: 100n; C_1206_3216Metric; LCSC C97946
J1: Conn_01x34; PinHeader_1x34_P2.54mm_Vertical
R1, R2, R3, R4: 150; R_1206_3216Metric; LCSC C25353
RV1: 50k; Potmeter_THT_Avans; LCSC AVANS
U1: SN74HC595DR; SOIC-16_L9.9-W3.9-P1.27-LS6.0-BL; LCSC C10092
U2, U3, U4, U5, U7, U8, U9, U10, U13, U14, U15, U16, U19, U20, U21, U22: K6-6271D04; LED_Button_AVANS; LCSC C693824
U6: SN74HC138DR; SOIC-16_L9.9-W3.9-P1.27-LS6.0-BL; LCSC C6818
U11, U12, U18, U23: BSN20BKR; SOT-23-3_L2.9-W1.3-P1.90-LS2.4-BR; LCSC C118033
U17: SN74HC04DR; SOIC-14_L8.7-W3.9-P1.27-LS6.0-BL; LCSC C6811
U24, U25, U26, U27, U28: MT-0-102-A101-M200-RS+PJ; SW-TH_MT-0-103-A101-M200-RS; LCSC C1788492

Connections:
4X4_LED_Buttons_Button_1: C2.1, J1.34, U2.3, U2.4
4X4_LED_Buttons_Button_2: C3.1, J1.33, U3.3, U3.4
4X4_LED_Buttons_Button_3: C4.1, J1.32, U4.3, U4.4
4X4_LED_Buttons_Button_4: C5.1, J1.31, U5.3, U5.4
4X4_LED_Buttons_Button_5: C6.1, J1.30, U7.3, U7.4
4X4_LED_Buttons_Button_6: C7.1, J1.29, U8.3, U8.4
4X4_LED_Buttons_Button_7: C8.1, J1.28, U9.3, U9.4
4X4_LED_Buttons_Button_8: C9.1, J1.27, U10.3, U10.4
4X4_LED_Buttons_Button_9: C11.1, J1.26, U13.3, U13.4
4X4_LED_Buttons_Button_10: C12.1, J1.25, U14.3, U14.4
4X4_LED_Buttons_Button_11: C13.1, J1.24, U15.3, U15.4
4X4_LED_Buttons_Button_12: C14.1, J1.23, U16.3, U16.4
4X4_LED_Buttons_Button_13: C15.1, J1.22, U19.3, U19.4
4X4_LED_Buttons_Button_14: C16.1, J1.21, U20.3, U20.4
4X4_LED_Buttons_Button_15: C17.1, J1.20, U21.3, U21.4
4X4_LED_Buttons_Button_16: C18.1, J1.19, U22.3, U22.4
4X4_LED_Buttons_MUX_A: J1.7, U6.1 (A)
4X4_LED_Buttons_MUX_B: J1.8, U6.2 (B)
4X4_LED_Buttons_shift_clock: J1.4, U1.11 (SRCLK)
4X4_LED_Buttons_shift_data_in: J1.6, U1.14 (SER)
4X4_LED_Buttons_shift_output_enable: J1.5, U1.12 (RCLK)
+3V3: C1.1, C10.1, C19.1, J1.2, RV1.3, U1.10 (SRCLR#), U1.16 (VCC), U6.6 (G1), U6.16 (VCC), U17.14 (VCC)
GND: C1.2, C2.2, C3.2, C4.2, C5.2, C6.2, C7.2, C8.2, C9.2, C10.2, C11.2, C12.2, C13.2, C14.2, C15.2, C16.2, C17.2, C18.2, C19.2, C20.1, C21.1, C22.1, C23.1, C24.1, C25.1, C26.1, C27.1, C28.1, C29.1, J1.1, RV1.1, U1.8 (GND), U1.13 (OE#), U2.1, U2.2, U3.1, U3.2, U4.1, U4.2, U5.1, U5.2, U6.3 (C), U6.4 (G2A#), U6.5 (G2B#), U6.8 (GND), U7.1, U7.2, U8.1, U8.2, U9.1, U9.2, U10.1, U10.2, U11.2 (S), U12.2 (S), U13.1, U13.2, U14.1, U14.2, U15.1, U15.2, U16.1, U16.2, U17.7 (GND), U17.11 (5A), U17.13 (6A), U18.2 (S), U19.1, U19.2, U20.1, U20.2, U21.1, U21.2, U22.1, U22.2, U23.2 (S), U24.2, U25.2, U26.2, U27.2, U28.2
unnamed: R1.1, U1.1 (QB)
unnamed: R2.1, U1.2 (QC)
unnamed: R3.2, U1.15 (QA)
unnamed: R4.1, U1.3 (QD)
Rotary_Switch: J1.3, RV1.2
Switches_Switch_1_OFF: C25.2, J1.17, U24.1
Switches_Switch_1_ON: C20.2, J1.18, U24.3
Switches_Switch_2_OFF: C26.2, J1.15, U25.1
Switches_Switch_2_ON: C21.2, J1.16, U25.3
Switches_Switch_3_OFF: C27.2, J1.13, U26.1
Switches_Switch_3_ON: C22.2, J1.14, U26.3
Switches_Switch_4_OFF: C28.2, J1.11, U27.1
Switches_Switch_4_ON: C23.2, J1.12, U27.3
Switches_Switch_5_OFF: C29.2, J1.9, U28.1
Switches_Switch_5_ON: C24.2, J1.10, U28.3
co_1: R3.1, U2.6, U7.6, U13.6, U19.6
co_2: R1.2, U3.6, U8.6, U14.6, U20.6
co_3: R2.2, U4.6, U9.6, U15.6, U21.6
co_4: R4.2, U5.6, U10.6, U16.6, U22.6
gate_ro_1: U11.1 (G), U17.2 (1Y)
gate_ro_1_inv: U6.15 (Y0), U17.1 (1A)
gate_ro_2: U12.1 (G), U17.4 (2Y)
gate_ro_2_inv: U6.14 (Y1), U17.3 (2A)
gate_ro_3: U17.6 (3Y), U18.1 (G)
gate_ro_3_inv: U6.13 (Y2), U17.5 (3A)
gate_ro_4: U17.8 (4Y), U23.1 (G)
gate_ro_4_inv: U6.12 (Y3), U17.9 (4A)
ro_1: U2.5, U3.5, U4.5, U5.5, U11.3 (D)
ro_2: U7.5, U8.5, U9.5, U10.5, U12.3 (D)
ro_3: U13.5, U14.5, U15.5, U16.5, U18.3 (D)
ro_4: U19.5, U20.5, U21.5, U22.5, U23.3 (D)

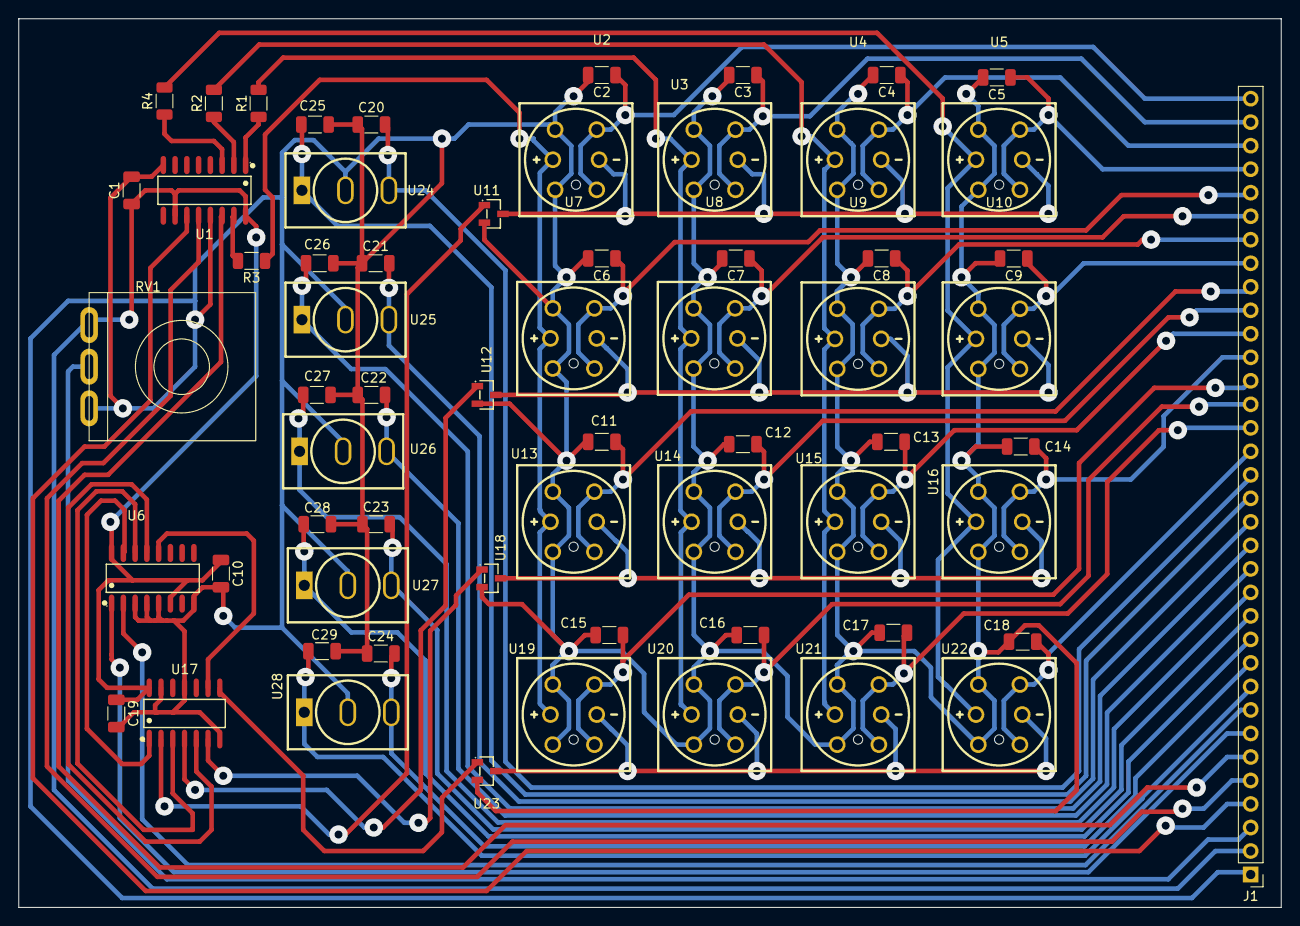
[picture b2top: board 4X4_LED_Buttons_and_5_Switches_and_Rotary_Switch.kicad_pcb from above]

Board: 2 copper layers, 136.4 x 96.0 mm, 63 parts (0 on the bottom side), 54 nets.

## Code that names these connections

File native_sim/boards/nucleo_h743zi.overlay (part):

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		BCD_A_7_Segment: gpiof_13 {
			gpios = <&gpiof 13 GPIO_ACTIVE_HIGH>;
		};
		battery_low_led: gpiob_2 {
			gpios = <&gpiob 2 GPIO_ACTIVE_HIGH>;
		};
		button_1_4x4: gpiob_0 {
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		switches_5_Off: gpiog_10 {
			gpios = <&gpiog 10 GPIO_PULL_UP>;
		};
		LCD_Display_E: gpiog_9 {
			gpios = <&gpiog 9 GPIO_ACTIVE_HIGH>;
		};
		LCD_Display_RS: gpiod_7 {
			gpios = <&gpiod 7 GPIO_ACTIVE_HIGH>;
		};
		LCD_Display_Backlight_Enable: gpiod_6 {
			gpios = <&gpiod 6 GPIO_ACTIVE_HIGH>;
		};
		start_Button: gpiod_5 {
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		start_Led: gpiod_4 {
			gpios = <&gpiod 4 GPIO_ACTIVE_HIGH>;
		};
		LCD_Display_D7: gpiod_3 {
			gpios = <&gpiod 3 GPIO_ACTIVE_HIGH>;
		};
		LCD_Display_D6: gpiod_2 {
			gpios = <&gpiod 2 GPIO_ACTIVE_HIGH>;
		};
		LCD_Display_D5: gpiod_1 {
			gpios = <&gpiod 1 GPIO_ACTIVE_HIGH>;
		};
		LCD_Display_D4: gpiod_0 {
			gpios = <&gpiod 0 GPIO_ACTIVE_HIGH>;
		};
		LCD_Display_D3: gpioc_12 {
			gpios = <&gpioc 12 GPIO_ACTIVE_HIGH>;
		};
		LCD_Display_D2: gpioc_11 {
			gpios = <&gpioc 11 GPIO_ACTIVE_HIGH>;
		};
		LCD_Display_D1: gpioc_10 {
			gpios = <&gpioc 10 GPIO_ACTIVE_HIGH>;
		};
		LCD_Display_D0: gpioa_15 {
			gpios = <&gpioa 15 GPIO_ACTIVE_HIGH>;
		};
		data_ready_3d_compass: gpioa_9 {
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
